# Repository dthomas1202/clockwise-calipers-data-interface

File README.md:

# Data Interface for Clockwise Tools Caliper Gauges

Easily transfer measurements from Clockwise Tools calipers to your computer for applications like measurement logging, CAD modeling, or manufacturing workflows.

This project is a reverse-engineered version of the Clockwise Tools DTCR-02 RS232 Data Cable for Clockwise tools DCLR-XX05 calipers.
And given the similarity to [liba2k's VINCA Reader](https://github.com/liba2k/VINCA_reader) it seems likely that this Data Interface will work with VINCA series calipers as well.

|  |
|:-:|
| *Data Interface connected to a iPhone running Excel.* |

## Table of Contents

- [Data Interface for Clockwise Tools Caliper Gauges](#data-interface-for-clockwise-tools-caliper-gauges)
  - [Table of Contents](#table-of-contents)
  - [Features](#features)
  - [Hardware](#hardware)
    - [Arduino Support](#arduino-support)
    - [PCB](#pcb)
    - [Case \& USB Cable](#case--usb-cable)
  - [Technical Information](#technical-information)
    - [The "RS232" Serial Protocol](#the-rs232-serial-protocol)
      - [Signal Details](#signal-details)
      - [Protocol Details](#protocol-details)
    - [Potential Improvements](#potential-improvements)
  - [Quirks](#quirks)
    - [iOS Devices](#ios-devices)
    - [Android Devices](#android-devices)

## Features

This project improves on the DTCR-02 Data Cable with enhanced features and flexibility:

- Emulates a generic USB keyboard, compatible with Linux, Windows, macOS, iOS[^1], Android[^1], and really anything that supports USB keyboards.
- Captures and transfers the caliper measurement to any program, such as Excel or CAD software.
- Multiple ways to trigger measurement transfer:
  - Built-in push button.
  - External remote push button or foot pedal (via a 2-pin JST connector).
  - Custom USB cable with a button near the calipers (see schematics for details).
- DIP switch configurable options:
  - `CTRL + A` to overwrite previous measurements.
  - Append units (mm/in) to measurements (e.g., 1.23&nbsp;mm).
  - Add newline, tab, comma, or space after measurements.
  - Enable a buzzer to provide audible feedback when a measurement is sent.
  - Enable the trigger input on the USB ports VBUS pin (see schematics for details).
- Open source allowing full customizability for advanced use cases.

[^1]: See [Quirks](#quirks) for compatibility notes.

## Hardware

|  |  |
|:-:|:-:|

### Arduino Support

Most Arduino's should be able to read the data stream from the calipers, as the clock rate is relatively slow.

However, in order to emulate a USB keyboard, the Arduino must support native USB communication (Micro, Pro Micro, Leonardo, etc.), or you must use something like [HoodLoader2](https://github.com/NicoHood/HoodLoader2) (See the [Arduino HID Project](https://github.com/NicoHood/HID) for compatibility).

### PCB

As part of the KiCad schematic, there is an example through-hole layout for a double-sided perfboard, as seen in the images above.

KiCad does not support making proper perfboard layouts, so the board is laid out as a PCB, but with components positioned on a 2.54&nbsp;mm grid.
If you intend fabricate an actual PCB, then you probably should not base it off of this.

### Case & USB Cable

3D models are also included for the case and the custom USB cable.
The case was designed to fit these [30x70&nbsp;mm perfboards](https://a.co/d/0OxZCzR) from Amazon, using the board layout provided in the schematic.

The USB cable was designed to fit a 6x6&nbsp;mm tactile push-button and a power only Micro-USB connector that I cut open to use the data pins.

> In both cases, you will likely have to make some modification to the 3D models to suit your own components.

|  |
|:-:|
| *Custom designed USB cable end with integrated trigger button* |

## Technical Information

### The "RS232" Serial Protocol

Clockwise Tools describes the communication as "RS232," but it uses synchronous serial communication over the USB D+ and D- pins. This is effectively equivalent to SPI.

#### Signal Details

- __Clock signal:__ USB D- pin, ~0.4&nbsp;ms per cycle, SPI Mode 3 equivalent.
- __Data signal:__ USB D+ pin, 24-bit (3 x 8-bit) packets, transmitted every ~150&nbsp;ms.
- __+1.5 V:__ USB VBUS pin, constant 1.5&nbsp;V supply.
- All pins operate at 1.5&nbsp;V.
- Clock and data are inverted due to the transistors used for level shifting. So SPI Mode 1 is used in software, and the serial data is inverted.
- Data is transmitted regardless of if the calipers are turned on or not.

> [!WARNING]
> The calipers exhibit weird behavior when too much current is drawn over the USB port.
> This can cause measurements to fluctuate significantly, or the screen to dim.
> Anything connected to the calipers USB port must not draw over __~0.3&nbsp;mA__ of current from all of its pins combined.
> This means that the parallel resistance between VBUS, D+, and D- to GND of the USB connector must be at least ~5&nbsp;kΩ, but preferably well above that.

As far as I can tell, there is no way to communicate from the host device to the calipers, as they are constantly transmitting on D+ and D-, and due to the above, pulling VBUS low causes the calipers to lose power.

#### Protocol Details

- First 4 bits are flags:
  - __Unit:__ Millimeters if 0, Inches if 1.
  - (Unknown use)
  - (Unknown use)
  - __Sign:__ Positive if 0, Negative if 1.
- Last 20 bits are fixed point measurement data:
  - In either hundredths of a millimeter, or
  - 1/2 thousandths of an inch.

The full details are laid out in this article: [Harbor Freight Caliper Data Format](https://www.yuriystoys.com/2013/07/chinese-caliper-data-format.html).

The calipers will send whatever unit is currently selected on the display.
Note that the fraction mode is sent exactly the same as inches.
However, it sends updates less often in fractions mode, presumably since it has to do additional processing for the fractional conversion.

The full implementation of decoding and converting the 24-bit packets can be seen in `ClockwiseCaliper.cpp`.

### Potential Improvements

I designed the schematics and built the device using parts that I had lying around.
Mostly used parts taken from laser printers, coffee makers, and power supplies.
So, given access to the right parts, there are some improvements that can be made to the design.

- The three transistors used to do the voltage level shifting (__Q1__, __Q2__, and __Q3__ in the schematic) should be replaced by MOSFETs.
  The resistors for those transistors should be changed to around 1&nbsp;kΩ.
  And pull-down resistors for the MOSFETs should be added, with values around 100&nbsp;kΩ. This is because of the maximum current requirement as outlined above.

- The calipers can not source over 0.3&nbsp;mA of current from all of its pins, however, I have not tested how much current (if any) it can sink.
  This may be the preferred method for connecting if it works.

- The program could technically use the hardware SPI interface of the Arduino.
  However, without proper timing of the slave select signal, it can cause the data to get out of sync on the first byte.
  This could be solved by controlling the SPI slave select input using another output pin.
  Then activating it on the initial clock pulse, and deactivating it on the last clock pulse.
  However, ensure that the slave select pin is accessible, as Arduino Pro Micro's use that pin for an onboard LED.

## Quirks

### iOS Devices

iOS devices will complain if the USB device reports that it draws more than 100&nbsp;mA over the USB port.
By default, most Arduino's report their bMaxPower USB configuration descriptor to be 500&nbsp;mA.

To change the bMaxPower descriptor you have to change the line `#define USB_CONFIG_POWER (500)` to be 100 or less in `USBCore.h` of the Arduino core files.

Note that for iDevices with a lightning port, a Lightning to USB Camera Adapter (the one with only a USB port) will allow connecting the device, so long as it reports a lower power consumption.

Instead, I have heard that the Lightning to USB 3 Camera Adapter (the one with both a USB port and a lightning port) MAY allow devices that report more than 100&nbsp;mA to work, so long as a charging cable is plugged in.

### Android Devices

I have not tested any Android devices with the Data Interface, but I would assume that with the right adapter, and potentially the iOS bMaxPower tweak above that it would work.

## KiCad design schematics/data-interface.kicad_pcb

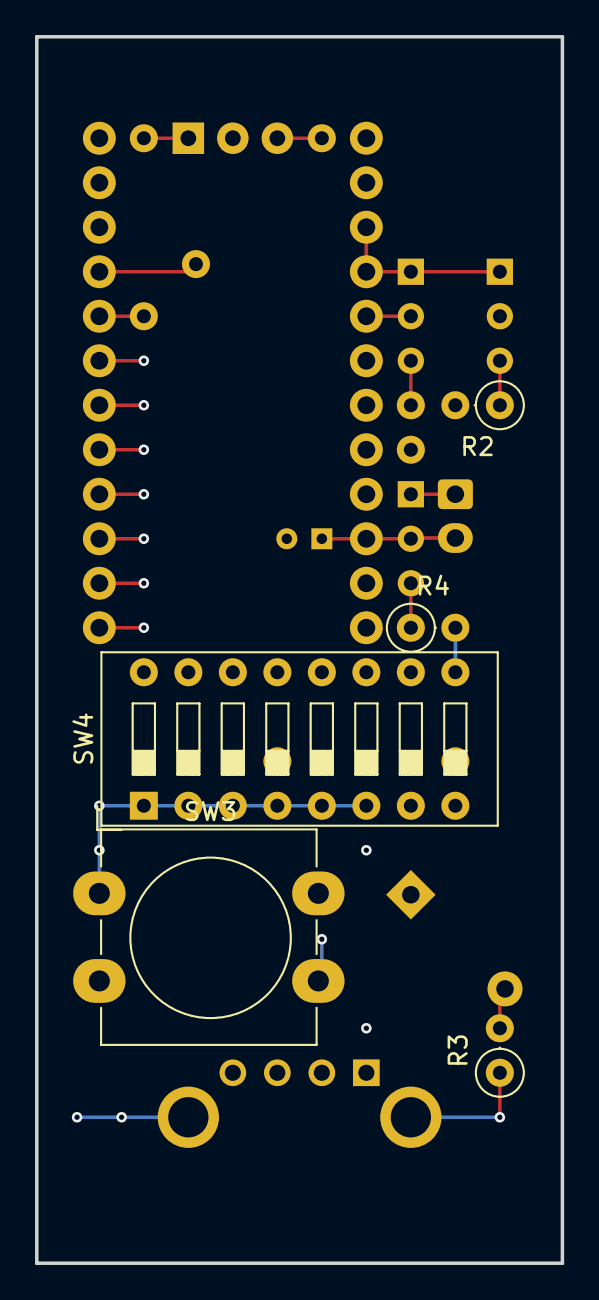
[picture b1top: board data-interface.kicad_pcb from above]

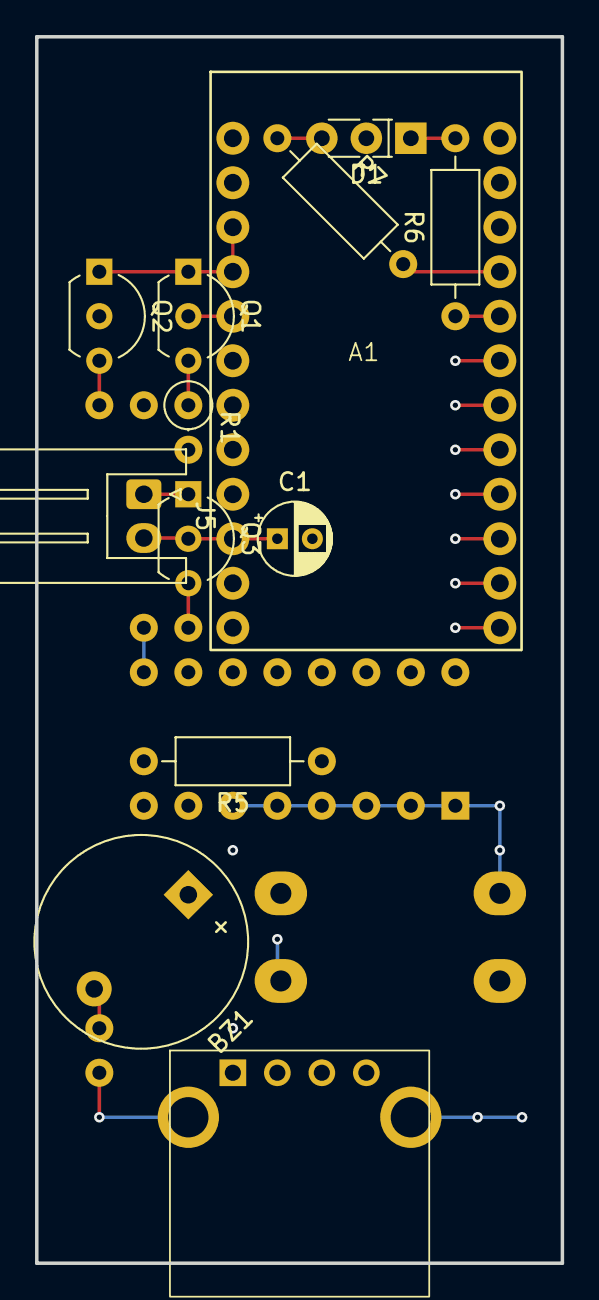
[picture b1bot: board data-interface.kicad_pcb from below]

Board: 4 copper layers, 30.0 x 70.0 mm, 18 parts (13 on the bottom side), 24 nets.

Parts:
A1: Qwiic_Pro_Micro_USB-C; Qwiic_Pro_Micro_USB-C_Socket
BZ1: Buzzer; Buzzer_12x9.5RM7.6
C1: 2.2uF; CP_Radial_D4.0mm_P2.00mm
D1: LED Red/Green; LED_Rectangular_W5.0mm_H2.0mm-3Pins
J2: USB_A; USB_A_Horizontal
J5: Trigger Button Input Connector; JST_XH_S2B-XH-A_1x02_P2.50mm_Horizontal
Q1, Q2, Q3: 2SC945; TO-92L_Inline_Wide
R1, R2, R4: 22K; R_Axial_DIN0207_L6.3mm_D2.5mm_P2.54mm_Vertical
R3: 470; R_Axial_DIN0207_L6.3mm_D2.5mm_P2.54mm_Vertical
R5: 47K; R_Axial_DIN0207_L6.3mm_D2.5mm_P10.16mm_Horizontal
R6: 220; R_Axial_DIN0207_L6.3mm_D2.5mm_P10.16mm_Horizontal
R7: 10K; R_Axial_DIN0207_L6.3mm_D2.5mm_P10.16mm_Horizontal
SW3: SW_Push; SW_PUSH-12mm_Wuerth-430476085716
SW4: SW_DIP_x08; SW_DIP_SPSTx08_Slide_9.78x22.5mm_W7.62mm_P2.54mm

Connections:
/sw1_buzzer: A1.D10 (D10/A10), SW4.10
/sw1_comma: A1.A1, SW4.12
/sw1_ctrl_a: A1.D16 (D16/MOSI), SW4.16
/sw1_newline: A1.D15 (D15/SCK), SW4.14
/sw1_space: A1.A2, SW4.11
/sw1_tab: A1.A0, SW4.13
/sw1_units: A1.D14 (D14/MISO), SW4.15
/sw1_usb_trigger: J2.1 (VBUS), SW4.8
GND: A1.GND0 (GND), A1.GND1 (GND), A1.GND2 (GND), C1.2, D1.2 (K), J2.4 (GND), J2.5 (Shield), J5.1, Q1.1 (E), Q2.1 (E), Q3.1 (E), R3.1, R5.1, SW3.1, SW4.1, SW4.2, SW4.3, SW4.4, SW4.5, SW4.6
unnamed: A1.D2 (D2/SDA), Q1.2 (C)
unnamed: A1.D3 (D3/SCL), Q2.2 (C)
unnamed: A1.A3, R6.1
unnamed: A1.5V (VCC), R7.2
unnamed: BZ1.1 (+), SW4.7
unnamed: BZ1.2 (-), R3.2
unnamed: D1.1 (A1), R6.2
unnamed: D1.3 (A2), R7.1
unnamed: J2.3 (D+), R1.2
unnamed: J2.2 (D-), R2.2
unnamed: A1.D7, C1.1, J5.2, Q3.2 (C), SW3.2
unnamed: Q1.3 (B), R1.1
unnamed: Q2.3 (B), R2.1
unnamed: Q3.3 (B), R4.1
unnamed: R4.2, R5.2, SW4.9

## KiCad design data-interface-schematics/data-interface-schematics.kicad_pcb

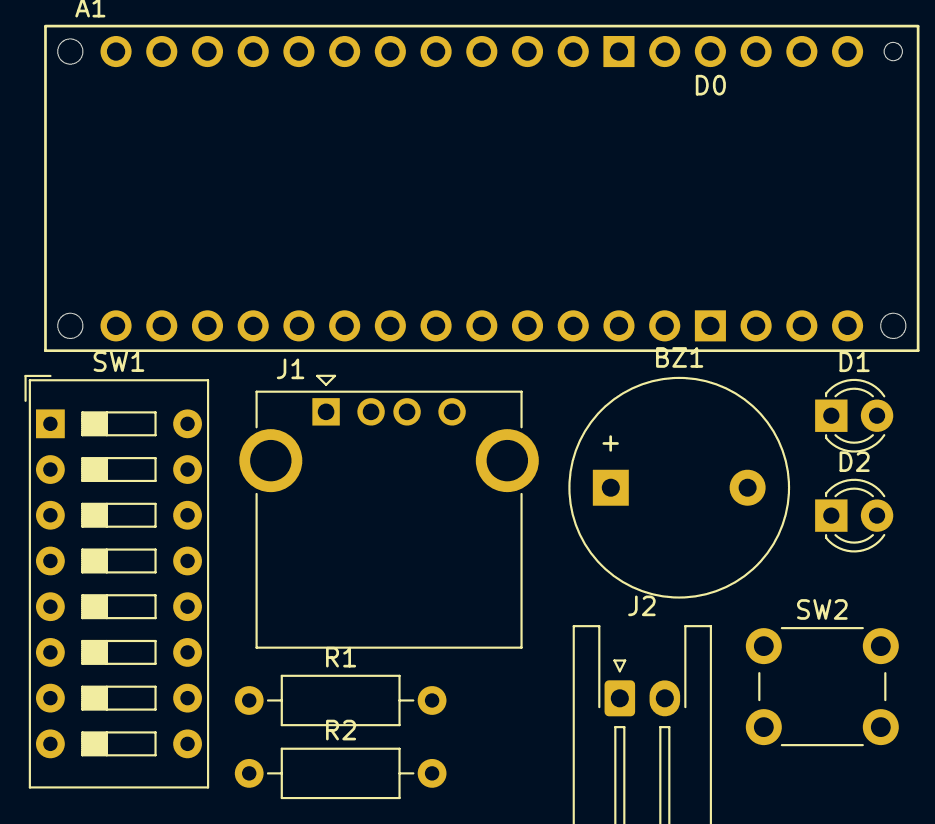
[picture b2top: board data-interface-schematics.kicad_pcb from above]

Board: 2 copper layers, 10 parts (0 on the bottom side), 17 nets, no tracks yet.

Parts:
A1: Arduino_Micro_Socket
BZ1: Buzzer; Buzzer_12x9.5RM7.6
D1: Power LED; LED_D3.0mm
D2: Data LED; LED_D3.0mm
J1: USB_A; USB_A_CONNFLY_DS1095-WNR0
J2: Trigger Button Input; JST_XH_S2B-XH-A-1_1x02_P2.50mm_Horizontal
R1, R2: 1K; R_Axial_DIN0207_L6.3mm_D2.5mm_P10.16mm_Horizontal
SW1: SW_DIP_x08; SW_DIP_SPSTx08_Slide_9.78x22.5mm_W7.62mm_P2.54mm
SW2: SW_Push; SW_PUSH_6mm

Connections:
GND: A1.GND1 (GND), A1.GND2 (GND), BZ1.2 (-), J1.4 (GND), J1.5 (Shield), J2.2, R1.2, R2.1, SW1.10, SW1.11, SW1.12, SW1.13, SW1.14, SW1.15, SW1.16, SW2.1
unnamed: A1.D7 (D7_INT4), SW1.4
unnamed: A1.D4, SW1.1
unnamed: A1.D5, SW1.2
unnamed: A1.D6, SW1.3
unnamed: A1.D8, SW1.5
unnamed: A1.D9, SW1.6
unnamed: A1.D10, SW1.7
unnamed: A1.D11, SW1.8
unnamed: A1.MOSI (SPI_MOSI), J1.2 (D-)
unnamed: A1.SCK (SPI_SCK), J1.3 (D+)
unnamed: BZ1.1 (+), SW1.9
unnamed: A1.5V, D1.2 (A)
unnamed: D1.1 (K), R2.2
unnamed: A1.D12, D2.2 (A)
unnamed: D2.1 (K), R1.1
unnamed: A1.A0, J2.1, SW2.2

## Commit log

2024-12-04 Work on schematic
2024-12-07 Changes to schematics
2024-12-19 Added mock 3D model of case, updated schematic
2024-12-25 Working code for getting caliper data
2025-01-05 Completed working code
2025-01-05 Renamed LICENSE file
2025-01-05 Updated schematics
2025-01-05 Added 3d models and blender files
2025-01-05 Update README (WIP)
2025-01-06 Fixed minor errors in schematics
2025-01-06 More work on README
2025-01-16 Work on README
2025-01-18 README
